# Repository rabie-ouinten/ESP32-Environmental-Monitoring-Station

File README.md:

# ESP32 Environmental Monitoring Station

## Overview

An environmental monitoring station based on the ESP32. It measures **temperature**, **relative humidity** and **light intensity**, shows the values locally on a 16×2 LCD, and serves a live **web dashboard** directly from the ESP32 (no router, no cloud).

The project combines embedded programming, sensor interfacing, a web interface, and a custom PCB designed in KiCad.

## Features

- Temperature and humidity measurement (DHT11)
- Light intensity measurement (LDR, raw 12-bit ADC value, 0–4095)
- Local display on a 16×2 LCD with I²C interface
- Built-in Wi-Fi access point: connect to the ESP32 and open the dashboard at `http://192.168.4.1`
- Live charts for temperature, humidity and light (last 20 measurements)
- Measurement every 2 seconds, stored in a circular buffer of 1000 records
- Data export in CSV format
- Custom schematic and PCB designed in KiCad (USB-C, battery charging, 3.3 V buck-boost supply)

## Hardware

### Prototype (tested)

|         Component        |       Details                  |
|     -----------------    |      -----------------         |
|      Microcontroller     | ESP32 development board (ESP-WROOM-32, "ESP32 Dev Module") |
|   Temperature / humidity |     DHT11 on GPIO 18           |
|       Light sensor       |     LDR on GPIO 34 (ADC input) |
|          Display         |     16×2 LCD with I²C backpack |

### Custom PCB (KiCad)

|       Block       | Components               |
|        ---        |     ---                  |
|  Microcontroller  | ESP32-S3-WROOM-1         |
|    USB-C input    | USB-C receptacle with CC1/CC2 resistors, fuse                       |
|     Protection    | USBLC6-2SC6 (ESD on data lines), TVS0500DRV (VBUS surge protection) |
|  Battery charging | TP4056 Li-ion charger with battery connector                        |
|   3.3 V supply    | TPS63001 buck-boost converter        |
|      Sensors      | DHT11, LDR voltage divider           |
|     Expansion     | I²C connector with pull-up resistors |
|   User controls   | BOOT and EN (reset) buttons          |

> **Note:** the firmware was developed and validated on an ESP32 development board. The PCB targets the ESP32-S3-WROOM-1; GPIO assignments may need to be adapted when moving the firmware to the custom board.

## Software and Tools

- Arduino IDE 2.3.7, C++ / Arduino framework
- ESP32 Wi-Fi web server (access point mode)
- HTML, CSS and JavaScript for the dashboard
- KiCad for schematic capture and PCB design

## Project Structure

```
.
├── firmware/    # ESP32 source code (Arduino sketch)
├── hardware/    # KiCad schematic and PCB design files
└── image/      # Screenshots, photos, project report
```

## Getting Started

1. Install the [Arduino IDE](https://www.arduino.cc/en/software).
2. Install the ESP32 board support package and select **ESP32 Dev Module**.
3. Install the required libraries: a DHT sensor library and an I²C LCD library (for example `DHT sensor library` and `LiquidCrystal_I2C`).
4. Open `firmware/station_environnementale/station_environnementale.ino`.
5. Check the pin definitions at the top of the sketch:
   ```cpp
   #define DHT_PIN   18
   #define DHT_TYPE  DHT11
   #define LDR_PIN   34
   ```
6. Upload the sketch to the ESP32.
7. Open the Serial Monitor at **9600 baud** to check the readings.
8. On your phone or computer, connect to the Wi-Fi network created by the ESP32, then open `http://192.168.4.1`.

## Wiring (prototype)

|     Signal     | ESP32 pin |
|       ---      |    ---    |
|  DHT11 data    |  GPIO 18  |
| LDR divider output | GPIO 34 |
|     LCD SDA    | GPIO 21 (default I²C) |
|     LCD SCL    | GPIO 22 (default I²C) |

Adjust the LCD pins and I²C address (commonly `0x27` or `0x3F`) to match your hardware.

## Configuration

|      Parameter       | Default |       Description        |
|         ---          |   ---   |          ---             |
| `SAMPLE_INTERVAL_MS` |   2000  |     Time between two measurements              |
|     `MAX_RECORDS`    |   1000  | Size of the circular buffer used for recording |

## Web Interface

- Live charts of temperature, humidity and light intensity
- History of the last 20 measurements
- CSV export of the recorded data

## Known Limitations

- The DHT11 has limited accuracy (about ±2 °C and ±5 % RH) and a slow response time.
- The LDR output is a raw ADC value and is **not calibrated** to lux.
- The 1000-record history is stored in RAM and is lost on reset or power loss.
- The PCB has not yet been fully validated.

## Future Improvements

- Calibrate the light measurement (ADC value to lux)
- Replace the DHT11 with a more accurate sensor such as the BME280 (I²C)
- Enhance the web interface
- Add new sensors through the I²C expansion connector
- Build and validate the custom PCB, then optimize the design

## License

This project is distributed under the license specified in the `LICENSE` file.

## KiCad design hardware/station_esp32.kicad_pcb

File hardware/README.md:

This directory contains the KiCad electronic schematic and PCB design files.

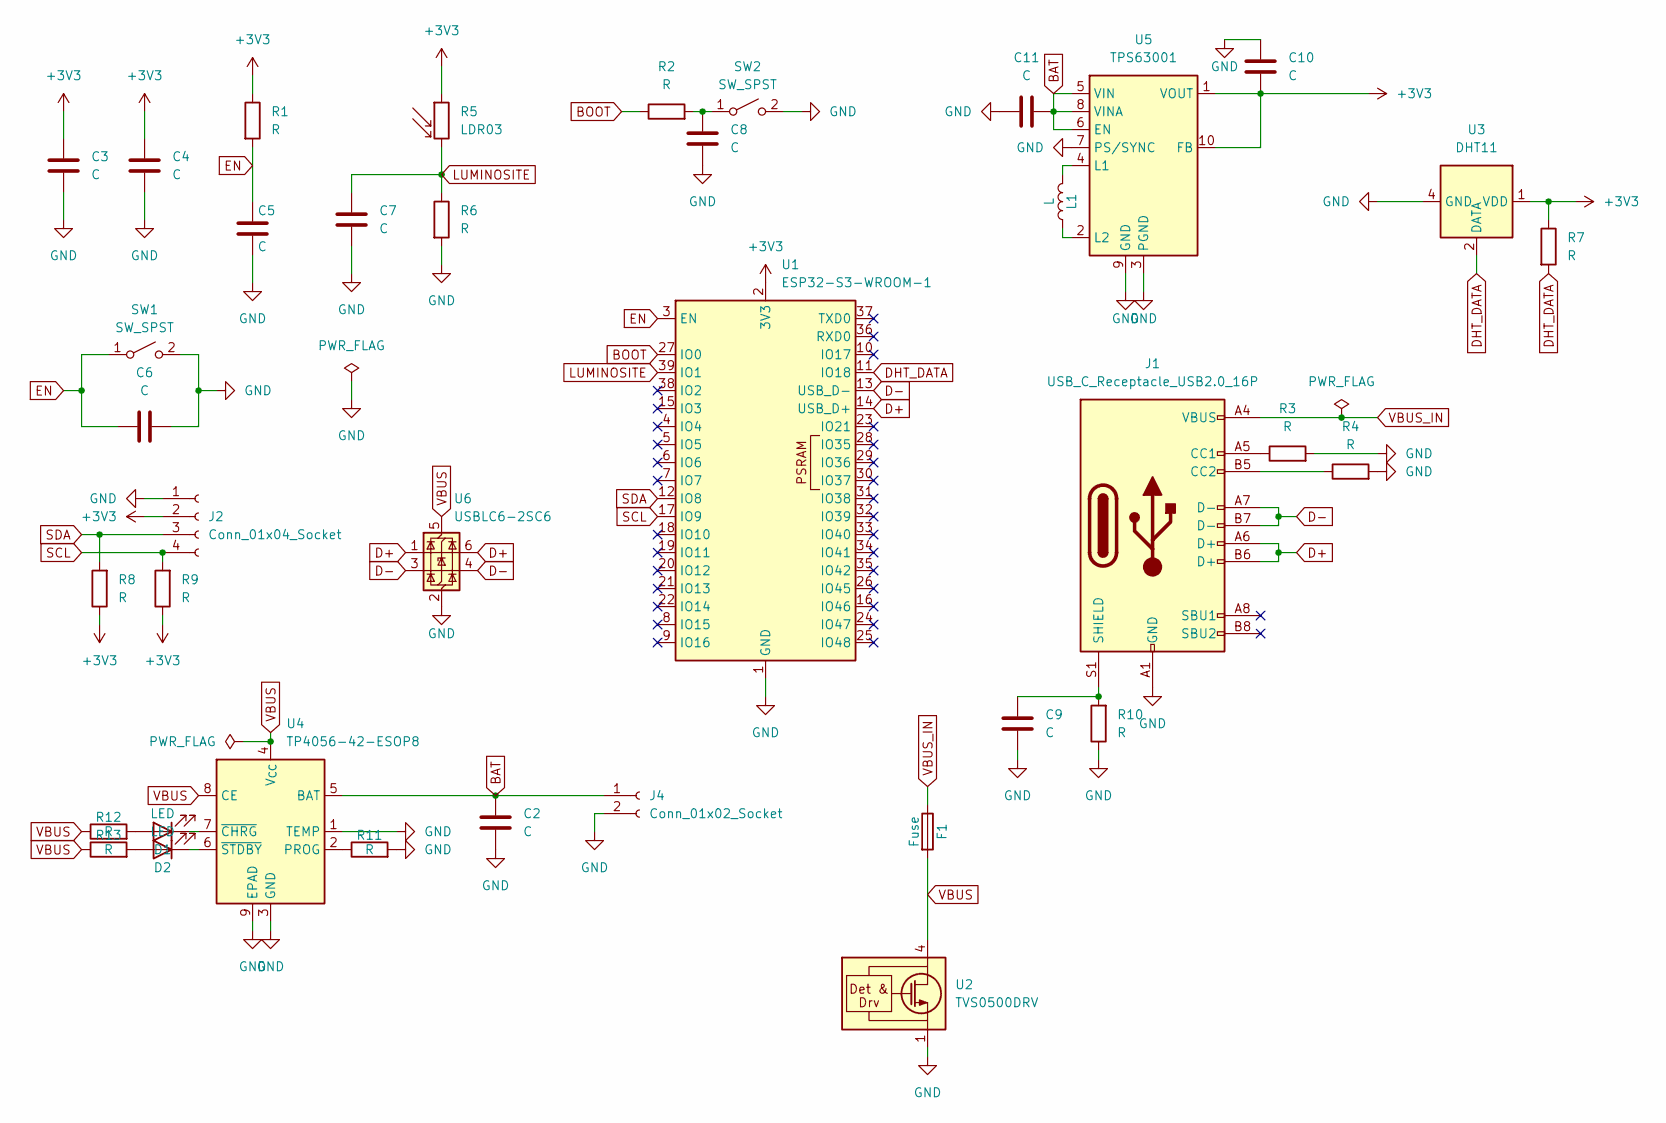
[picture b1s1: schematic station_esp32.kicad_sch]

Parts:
C2, C3, C4, C5, C6, C7, C8, C9, C10, C11: C; C_0805_2012Metric
D1, D2: LED; LED_0805_2012Metric
F1: Fuse; Fuse_0805_2012Metric
J1: USB_C_Receptacle_USB2.0_16P; USB_C_Receptacle_GCT_USB4105-xx-A_16P_TopMnt_Horizontal
J2: Conn_01x04_Socket; JST_PH_B4B-PH-K_1x04_P2.00mm_Vertical
J4: Conn_01x02_Socket; JST_PH_B2B-PH-K_1x02_P2.00mm_Vertical
L1: L; L_0805_2012Metric
R1, R2, R3, R4, R6, R7, R8, R9, R10, R11, R12, R13: R; R_0805_2012Metric
R5: LDR03; R_LDR_10x8.5mm_P7.6mm_Vertical
SW1, SW2: SW_SPST; SW_SPST_B3U-1000P
U1: ESP32-S3-WROOM-1
U2: TVS0500DRV; WSON-6-1EP_2x2mm_P0.65mm_EP1x1.6mm
U3: DHT11; Aosong_DHT11_5.5x12.0_P2.54mm
U4: TP4056-42-ESOP8; SOIC-8-1EP_3.9x4.9mm_P1.27mm_EP2.41x3.3mm_ThermalVias
U5: TPS63001; Texas_DRC0010J_ThermalVias
U6: USBLC6-2SC6; SOT-23-6

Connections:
+3V3: C3.1, C4.1, C10.2, J2.2, R1.1, R5.1, R7.1, R8.1, R9.1, U1.2 (3V3), U3.1 (VDD), U5.1 (VOUT), U5.10 (FB)
BAT: C2.1, C11.2, J4.1, U4.5 (BAT), U5.5 (VIN), U5.6 (EN), U5.8 (VINA)
BOOT: R2.1, U1.27 (IO0)
D+: J1.A6 (D+), J1.B6 (D+), U1.14 (USB_D+), U6.1 (I/O1), U6.6 (I/O1)
D-: J1.A7 (D-), J1.B7 (D-), U1.13 (USB_D-), U6.3 (I/O2), U6.4 (I/O2)
DHT_DATA: R7.2, U1.11 (IO18), U3.2 (DATA)
EN: C5.1, C6.1, R1.2, SW1.1 (A), U1.3 (EN)
GND: C2.2, C3.2, C4.2, C5.2, C6.2, C7.2, C8.2, C9.2, C10.1, C11.1, J1.A1 (GND), J1.A12 (GND), J1.B1 (GND), J1.B12 (GND), J2.1, J4.2, R3.2, R4.2, R6.2, R10.1, R11.2, SW1.2 (B), SW2.2 (B), U1.1 (GND), U1.40 (GND), U1.41 (GND), U2.1 (GND), U2.2 (GND), U2.3 (GND), U2.7 (GND), U3.4 (GND), U4.1 (TEMP), U4.3 (GND), U4.9 (EPAD), U5.3 (PGND), U5.7 (PS/SYNC), U5.9 (GND), U5.11 (PGND), U6.2 (GND)
LUMINOSITE: C7.1, R5.2, R6.1, U1.39 (IO1)
unnamed: D1.2 (A), R12.2
unnamed: D1.1 (K), U4.7 (~CHRG)
unnamed: D2.2 (A), R13.2
unnamed: D2.1 (K), U4.6 (~STDBY)
unnamed: J1.A5 (CC1), R3.1
unnamed: J1.B5 (CC2), R4.1
unnamed: C9.1, J1.S1 (SHIELD), R10.2
unnamed: C8.1, R2.2, SW2.1 (A)
unnamed: R11.1, U4.2 (PROG)
unnamed: L1.2, U5.4 (L1)
unnamed: L1.1, U5.2 (L2)
SCL: J2.4, R9.2, U1.17 (IO9)
SDA: J2.3, R8.2, U1.12 (IO8)
VBUS: F1.2, R12.1, R13.1, U2.4 (IN), U2.5 (IN), U2.6 (IN), U4.4 (V_{CC}), U4.8 (CE), U6.5 (VBUS)
VBUS_IN: F1.1, J1.A4 (VBUS), J1.A9 (VBUS), J1.B4 (VBUS), J1.B9 (VBUS)

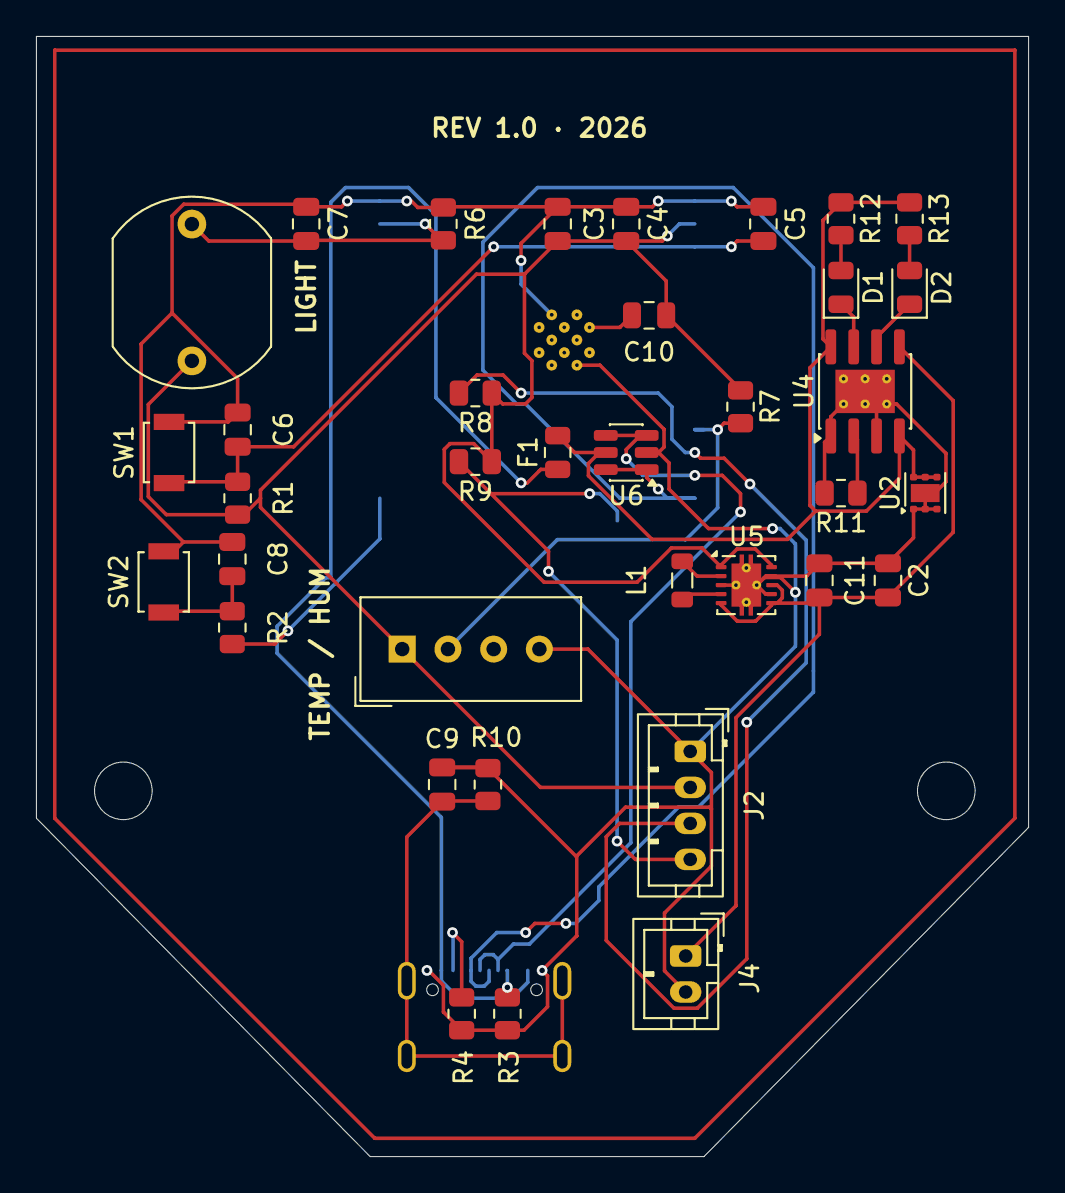
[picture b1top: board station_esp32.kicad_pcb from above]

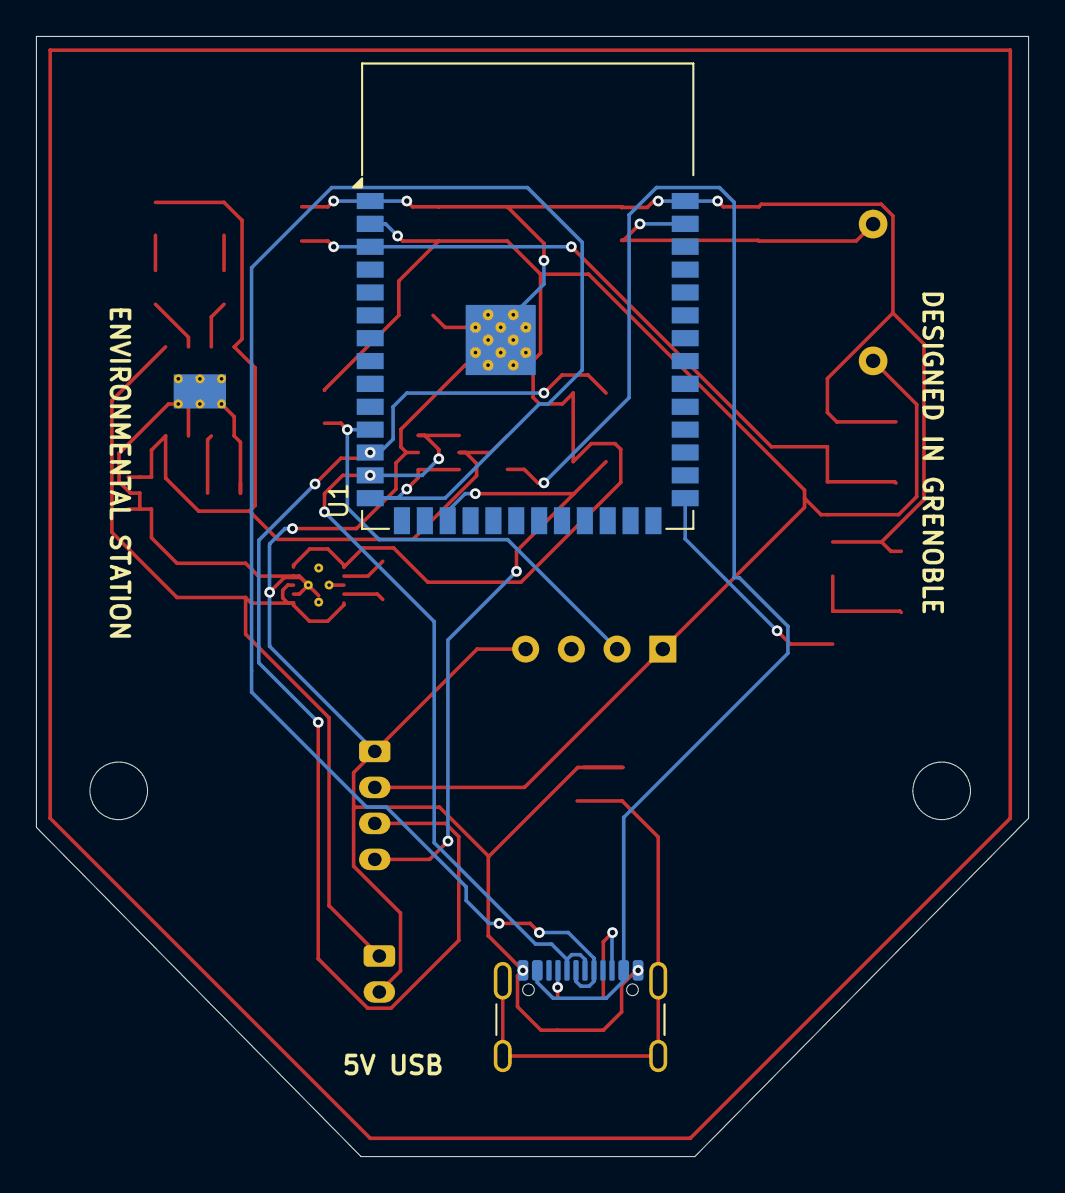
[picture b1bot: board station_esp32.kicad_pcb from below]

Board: 2 copper layers, 55.1 x 62.2 mm, 38 parts (2 on the bottom side), 24 nets.
